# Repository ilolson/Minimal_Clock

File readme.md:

# Minimal Clock
Small analog style clock made with an STM32 and a 72 LED charlieplex, uses 0201 LED's.
Has 2 buttons and the LSM6DSO IMU as input.
Powered by a CR2032 battery, the battery life lasts about 2-3 days,
this is without any sleep state optimization. 
It is only 28mm in diameter.

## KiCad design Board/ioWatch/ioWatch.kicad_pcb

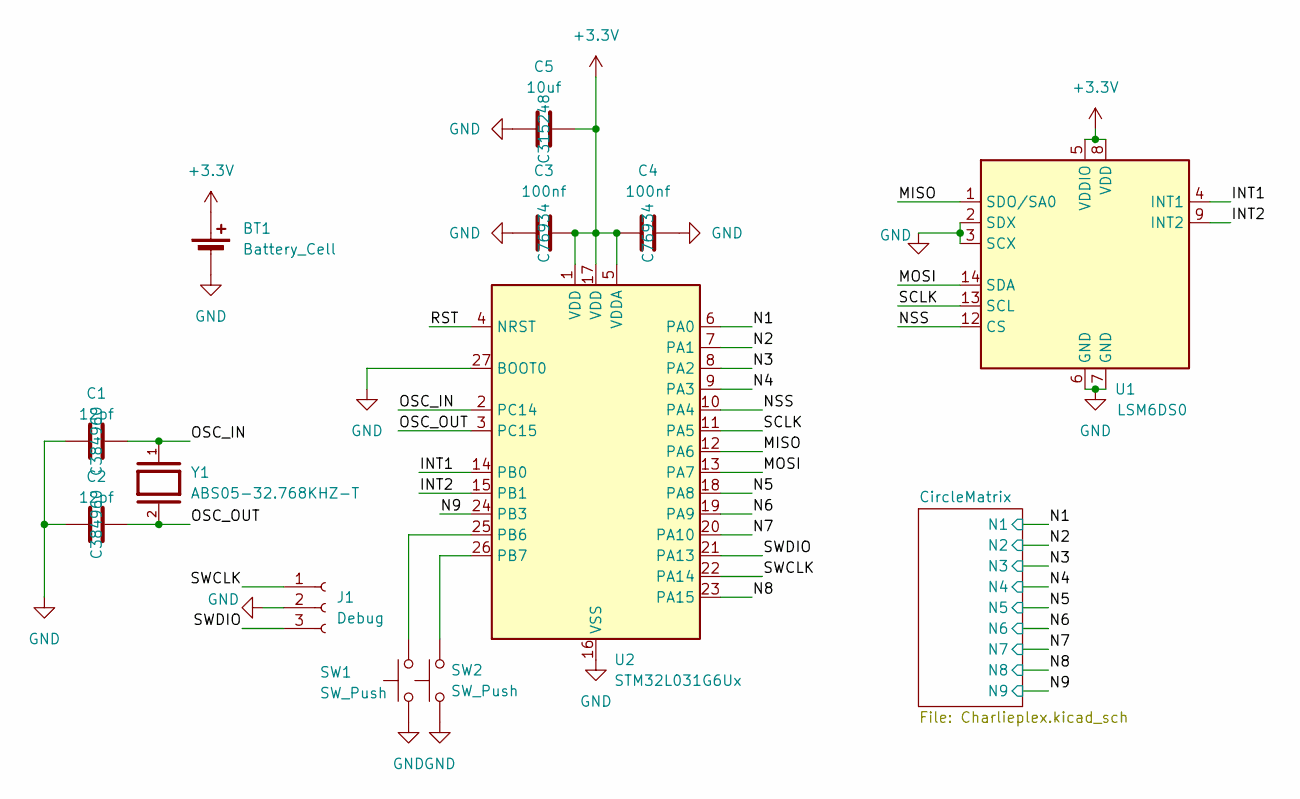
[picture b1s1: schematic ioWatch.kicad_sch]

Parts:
BT1: Battery_Cell; BatteryHolder_MPD_BC2003_1x2032; LCSC na
C1, C2: 12pf; C_0201_0603Metric; LCSC C384960
C3, C4: 100nf; C_0201_0603Metric; LCSC C76934
C5: 10uf; C_0402_1005Metric; LCSC C315248
J1: Debug; JST_SH_BM03B-SRSS-TB_1x03-1MP_P1.00mm_Vertical; LCSC na
SW1, SW2: SW_Push; ts1088; LCSC C720477
U1: LSM6DS0; LGA-14_3x2.5mm_P0.5mm_LayoutBorder3x4y; LCSC C2829074
U2: STM32L031G6Ux; QFN-28_4x4mm_P0.5mm; LCSC C96514
Y1: ABS05-32.768KHZ-T; XTAL_ABS05-32.768KHZ-T; PARTREV 11/3/2021; LCSC C179633

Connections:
+3.3V: BT1.1 (+), C3.2, C4.1, C5.1, U1.5 (VDDIO), U1.8 (VDD), U2.1 (VDD), U2.5 (VDDA), U2.17 (VDD)
/INT1: U1.4 (INT1), U2.14 (PB0)
/INT2: U1.9 (INT2), U2.15 (PB1)
/MISO: U1.1 (SDO/SA0), U2.12 (PA6)
/MOSI: U1.14 (SDA), U2.13 (PA7)
/N1: U2.6 (PA0); also elsewhere on the board
/N2: U2.7 (PA1); also elsewhere on the board
/N3: U2.8 (PA2); also elsewhere on the board
/N4: U2.9 (PA3); also elsewhere on the board
/N5: U2.18 (PA8); also elsewhere on the board
/N6: U2.19 (PA9); also elsewhere on the board
/N7: U2.20 (PA10); also elsewhere on the board
/N8: U2.23 (PA15); also elsewhere on the board
/N9: U2.24 (PB3); also elsewhere on the board
/NSS: U1.12 (CS), U2.10 (PA4)
/OSC_IN: C1.2, U2.2 (PC14), Y1.1
/OSC_OUT: C2.2, U2.3 (PC15), Y1.2
/RST: U2.4 (NRST)
/SCLK: U1.13 (SCL), U2.11 (PA5)
/SWCLK: J1.1, U2.22 (PA14)
/SWDIO: J1.3, U2.21 (PA13)
GND: BT1.2 (-), C1.1, C2.1, C3.1, C4.2, C5.2, J1.2, SW1.1, SW2.1, U1.2 (SDX), U1.3 (SCX), U1.6 (GND), U1.7 (GND), U2.16 (VSS), U2.27 (BOOT0), U2.28 (VSS)
unnamed: SW1.2, U2.25 (PB6)
unnamed: SW2.2, U2.26 (PB7)

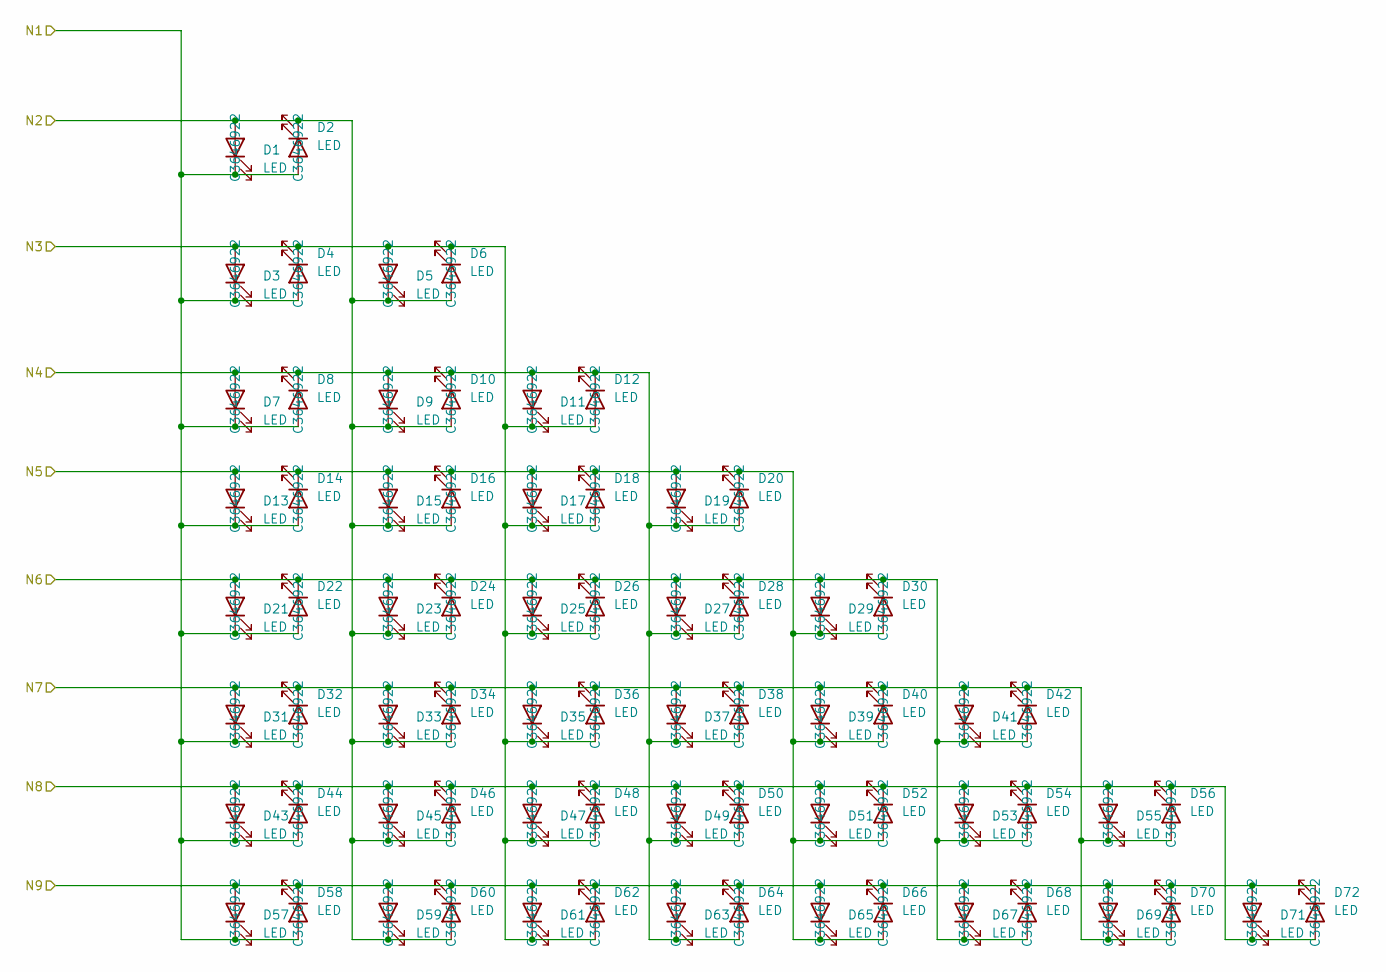
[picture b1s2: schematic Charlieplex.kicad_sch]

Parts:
D1, D2, D3, D4, D5, D6, D7, D8, D9, D10, D11, D12, D13, D14, D15, D16, D17, D18, D19, D20, D21, D22, D23, D24, D25, D26, D27, D28, D29, D30, D31, D32, D33, D34, D35, D36, D37, D38, D39, D40, D41, D42, D43, D44, D45, D46, D47, D48, D49, D50, D51, D52, D53, D54, D55, D56, D57, D58, D59, D60, D61, D62, D63, D64, D65, D66, D67, D68, D69, D70, D71, D72: LED; LED_0201_0603Metric; LCSC C3646922

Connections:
/N1: D1.1 (K), D2.2 (A), D3.1 (K), D4.2 (A), D7.1 (K), D8.2 (A), D13.1 (K), D14.2 (A), D21.1 (K), D22.2 (A), D31.1 (K), D32.2 (A), D43.1 (K), D44.2 (A), D57.1 (K), D58.2 (A); also elsewhere on the board
/N2: D1.2 (A), D2.1 (K), D5.1 (K), D6.2 (A), D9.1 (K), D10.2 (A), D15.1 (K), D16.2 (A), D23.1 (K), D24.2 (A), D33.1 (K), D34.2 (A), D45.1 (K), D46.2 (A), D59.1 (K), D60.2 (A); also elsewhere on the board
/N3: D3.2 (A), D4.1 (K), D5.2 (A), D6.1 (K), D11.1 (K), D12.2 (A), D17.1 (K), D18.2 (A), D25.1 (K), D26.2 (A), D35.1 (K), D36.2 (A), D47.1 (K), D48.2 (A), D61.1 (K), D62.2 (A); also elsewhere on the board
/N4: D7.2 (A), D8.1 (K), D9.2 (A), D10.1 (K), D11.2 (A), D12.1 (K), D19.1 (K), D20.2 (A), D27.1 (K), D28.2 (A), D37.1 (K), D38.2 (A), D49.1 (K), D50.2 (A), D63.1 (K), D64.2 (A); also elsewhere on the board
/N5: D13.2 (A), D14.1 (K), D15.2 (A), D16.1 (K), D17.2 (A), D18.1 (K), D19.2 (A), D20.1 (K), D29.1 (K), D30.2 (A), D39.1 (K), D40.2 (A), D51.1 (K), D52.2 (A), D65.1 (K), D66.2 (A); also elsewhere on the board
/N6: D21.2 (A), D22.1 (K), D23.2 (A), D24.1 (K), D25.2 (A), D26.1 (K), D27.2 (A), D28.1 (K), D29.2 (A), D30.1 (K), D41.1 (K), D42.2 (A), D53.1 (K), D54.2 (A), D67.1 (K), D68.2 (A); also elsewhere on the board
/N7: D31.2 (A), D32.1 (K), D33.2 (A), D34.1 (K), D35.2 (A), D36.1 (K), D37.2 (A), D38.1 (K), D39.2 (A), D40.1 (K), D41.2 (A), D42.1 (K), D55.1 (K), D56.2 (A), D69.1 (K), D70.2 (A); also elsewhere on the board
/N8: D43.2 (A), D44.1 (K), D45.2 (A), D46.1 (K), D47.2 (A), D48.1 (K), D49.2 (A), D50.1 (K), D51.2 (A), D52.1 (K), D53.2 (A), D54.1 (K), D55.2 (A), D56.1 (K), D71.1 (K), D72.2 (A); also elsewhere on the board
/N9: D57.2 (A), D58.1 (K), D59.2 (A), D60.1 (K), D61.2 (A), D62.1 (K), D63.2 (A), D64.1 (K), D65.2 (A), D66.1 (K), D67.2 (A), D68.1 (K), D69.2 (A), D70.1 (K), D71.2 (A), D72.1 (K); also elsewhere on the board

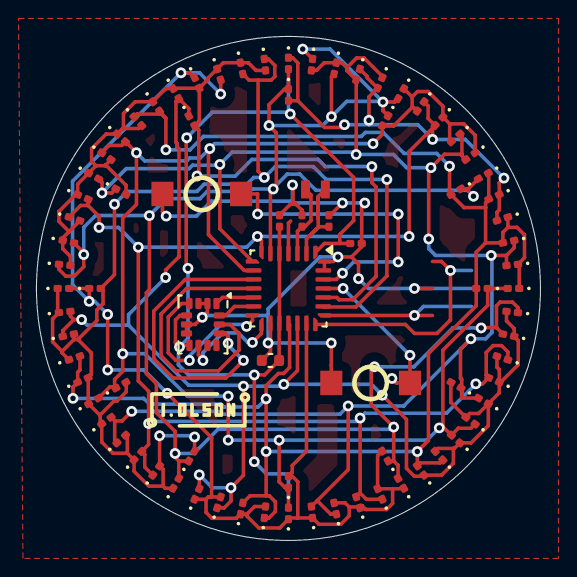
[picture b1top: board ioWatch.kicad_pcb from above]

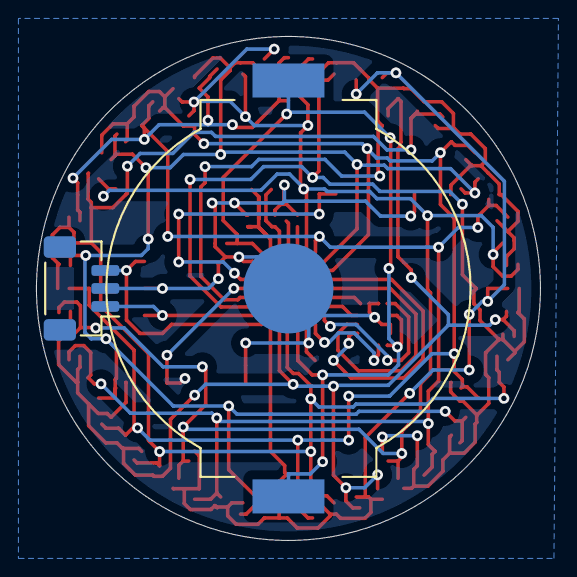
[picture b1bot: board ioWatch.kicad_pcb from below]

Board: 2 copper layers, 28.0 x 28.0 mm, 84 parts (2 on the bottom side), 23 nets.

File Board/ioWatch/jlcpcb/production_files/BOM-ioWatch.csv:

Comment,Designator,Footprint,LCSC,Quantity
ABS05-32.768KHZ-T,Y1,XTAL_ABS05-32.768KHZ-T,C179633,1
LSM6DS0,U1,LGA-14_3x2.5mm_P0.5mm_LayoutBorder3x4y,C2829074,1
10uf,C5,C_0402_1005Metric,C315248,1
LED,"D1,D10,D11,D12,D13,D14,D15,D16,D17,D18,D19,D2,D20,D21,D22,D23,D24,D25,D26,D27,D28,D29,D3,D30,D31,D32,D33,D34,D35,D36,D37,D38,D39,D4,D40,D41,D42,D43,D44,D45,D46,D47,D48,D49,D5,D50,D51,D52,D53,D54,D55,D56,D57,D58,D59,D6,D60,D61,D62,D63,D64,D65,D66,D67,D68,D69,D7,D70,D71,D72,D8,D9",LED_0201_0603Metric,C3646922,72
12pf,"C1,C2",C_0201_0603Metric,C384960,2
SW_Push,"SW1,SW2",ts1088,C720477,2
100nf,"C3,C4",C_0201_0603Metric,C76934,2
STM32L031G6Ux,U2,QFN-28_4x4mm_P0.5mm,C96514,1
Battery_Cell,BT1,BatteryHolder_MPD_BC2003_1x2032,,1
Debug,J1,JST_SH_BM03B-SRSS-TB_1x03-1MP_P1.00mm_Vertical,,1

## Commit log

2025-08-01 work
